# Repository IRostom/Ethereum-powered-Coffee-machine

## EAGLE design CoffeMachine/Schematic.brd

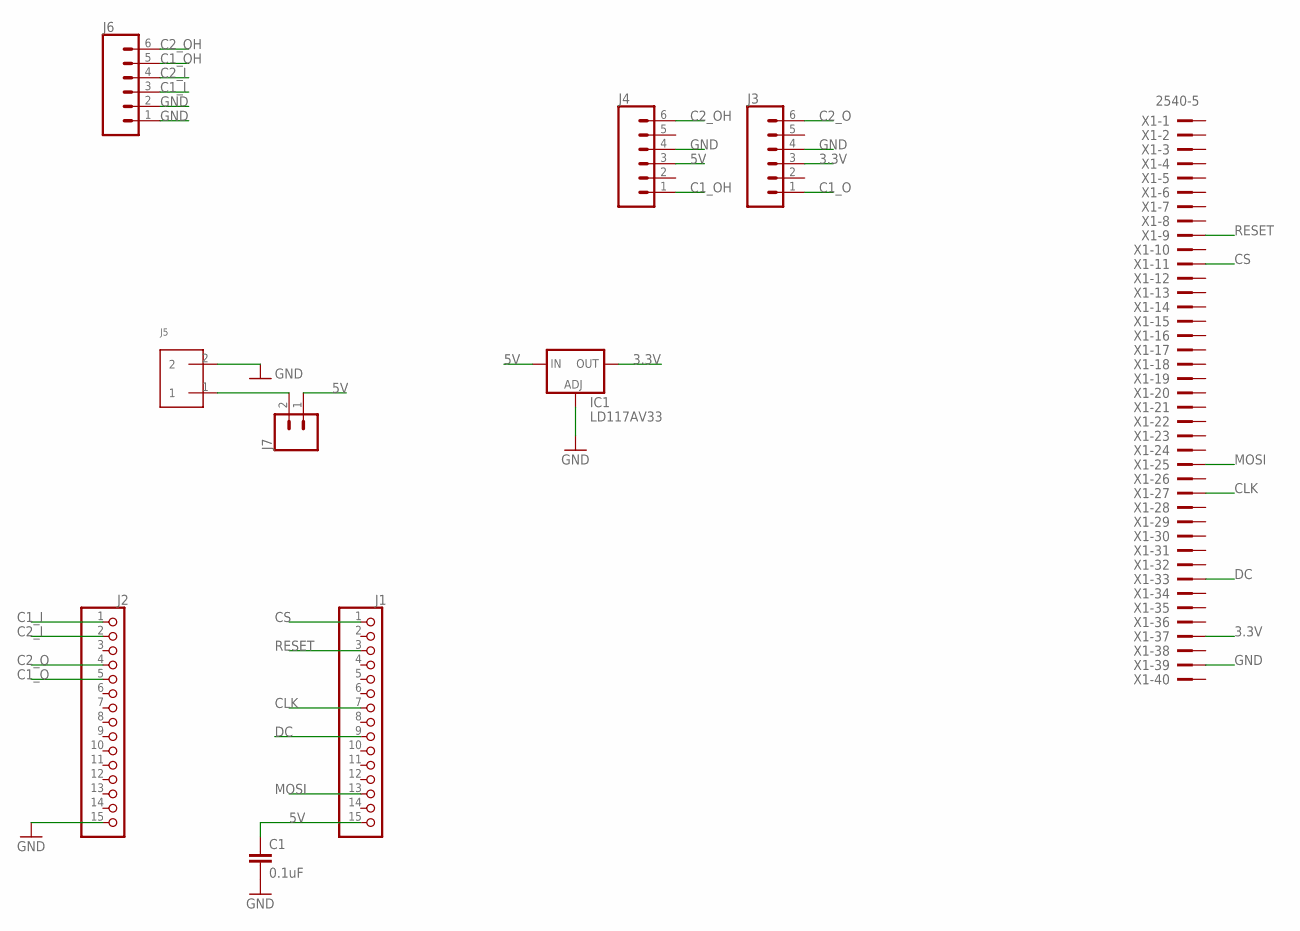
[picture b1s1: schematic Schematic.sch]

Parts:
C1: 0.1uF; CAP-PTH-SMALL-KIT
IC1: LD117AV33; TO220L1
J1, J2: PINHD-1X15; 1X15
J3, J4, J6: CONN_06LONGPADS; 1X06_LONGPADS
J5: SCREW_TERMINAL; PHEONIX-1935161
J7: CONN_02; 1X02
X1: 2540-5; PAK100/2500-5-40

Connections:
3.3V: IC1.2 (OUT), J3.3, X1.37
5V: C1.1, IC1.3 (IN), J1.15, J4.3, J7.1
C1_I: J2.1, J6.3
C1_O: J2.5, J3.1
C1_OH: J4.1, J6.5
C2_I: J2.2, J6.4
C2_O: J2.4, J3.6
C2_OH: J4.6, J6.6
CLK: J1.7, X1.27
CS: J1.1, X1.11
DC: J1.9, X1.33
GND: C1.2, IC1.1 (ADJ), J2.15, J3.4, J4.4, J5.2, J6.1, J6.2, X1.39
MOSI: J1.13, X1.25
unnamed: J5.1, J7.2
RESET: J1.3, X1.9

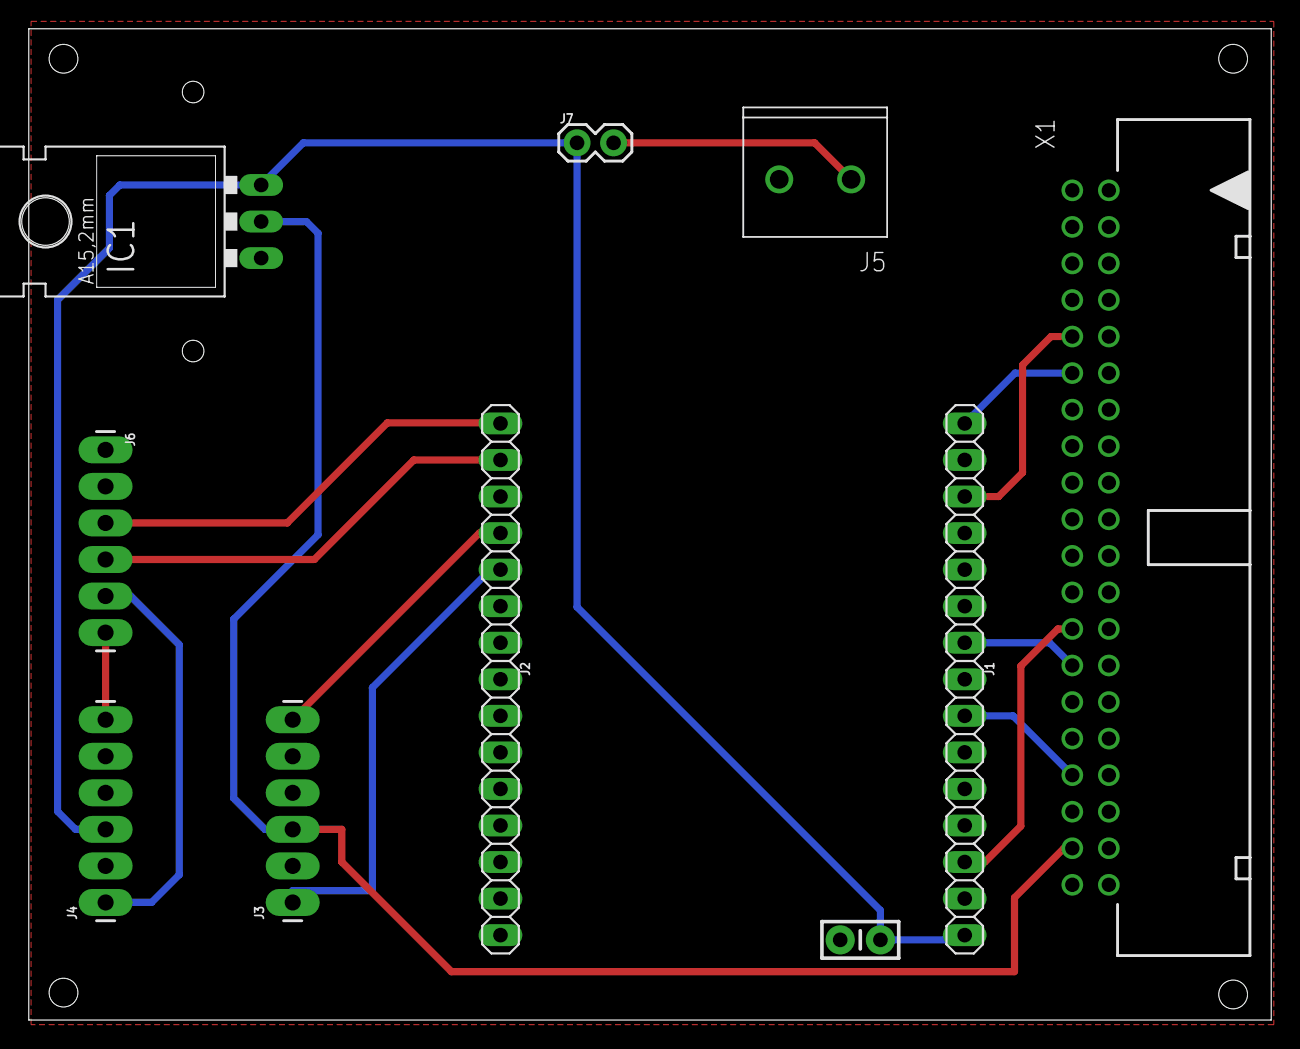
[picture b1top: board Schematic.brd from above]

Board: 2 copper layers, 86.3 x 68.9 mm, 10 parts (0 on the bottom side), 15 nets.

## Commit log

2019-03-24 First and Last commit

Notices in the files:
parts and their libraries:
SparkFun-Connectors: Licensing: Creative Commons ShareAlike 4.0 International - https://creativecommons.org/licenses/by-sa/4.0
